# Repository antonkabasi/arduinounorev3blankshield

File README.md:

# arduinounorev3blankshield

KiCAD Arduino Uno Rev 3 Blank shield template with pin headers, mounting holes and net connections.

Pin header connections are labeled as nets connected to their corresponding Arduino pins.

To use the template:
1. File\Open project
2. Open schematic editor
3. Add your own components and connect them to corresponding nets in the Schematic Editor
4. Assemble your PCB using the PCB editor

To learn more check "How to Make Custom Arduino Shield in 2 Hours | Full Tutorial" by Robert Feranec on Youtube.

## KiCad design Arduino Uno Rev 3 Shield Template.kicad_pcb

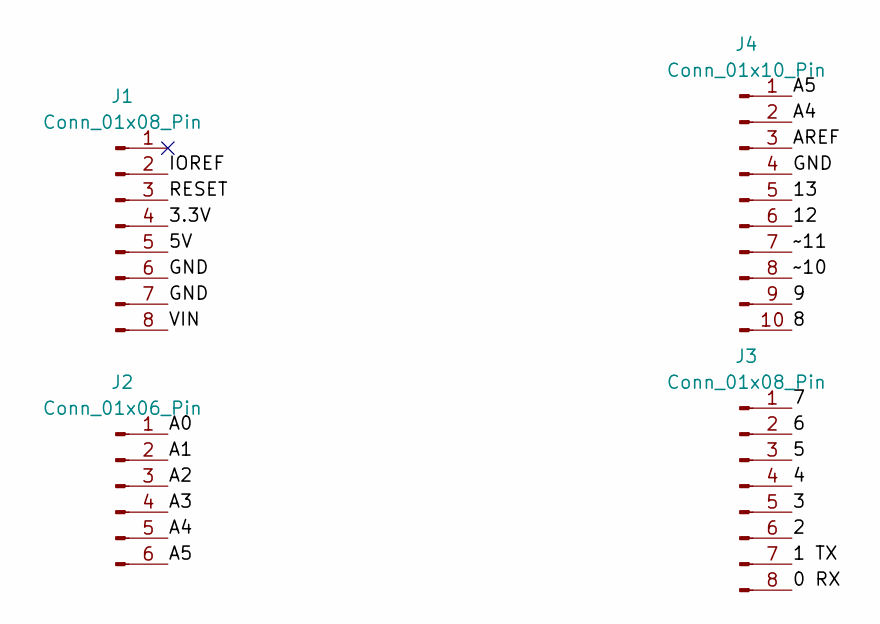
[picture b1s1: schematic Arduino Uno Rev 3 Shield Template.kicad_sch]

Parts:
J1, J3: Conn_01x08_Pin; PinSocket_1x08_P2.54mm_Vertical
J2: Conn_01x06_Pin; PinSocket_1x06_P2.54mm_Vertical
J4: Conn_01x10_Pin; PinSocket_1x10_P2.54mm_Vertical

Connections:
/0 RX: J3.8
/1 TX: J3.7
/2: J3.6
/3: J3.5
/3.3V: J1.4
/4: J3.4
/5: J3.3
/5V: J1.5
/6: J3.2
/7: J3.1
/8: J4.10
/9: J4.9
/12: J4.6
/13: J4.5
/A0: J2.1
/A1: J2.2
/A2: J2.3
/A3: J2.4
/A4: J2.5, J4.2
/A5: J2.6, J4.1
/AREF: J4.3
/GND: J1.6, J1.7, J4.4
/IOREF: J1.2
/RESET: J1.3
/VIN: J1.8
/~10: J4.8
/~11: J4.7

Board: 2 copper layers, 4 parts (0 on the bottom side), 3 nets, no tracks yet.

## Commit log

2023-12-09 Added files
2023-12-09 Added description and block to schematic
